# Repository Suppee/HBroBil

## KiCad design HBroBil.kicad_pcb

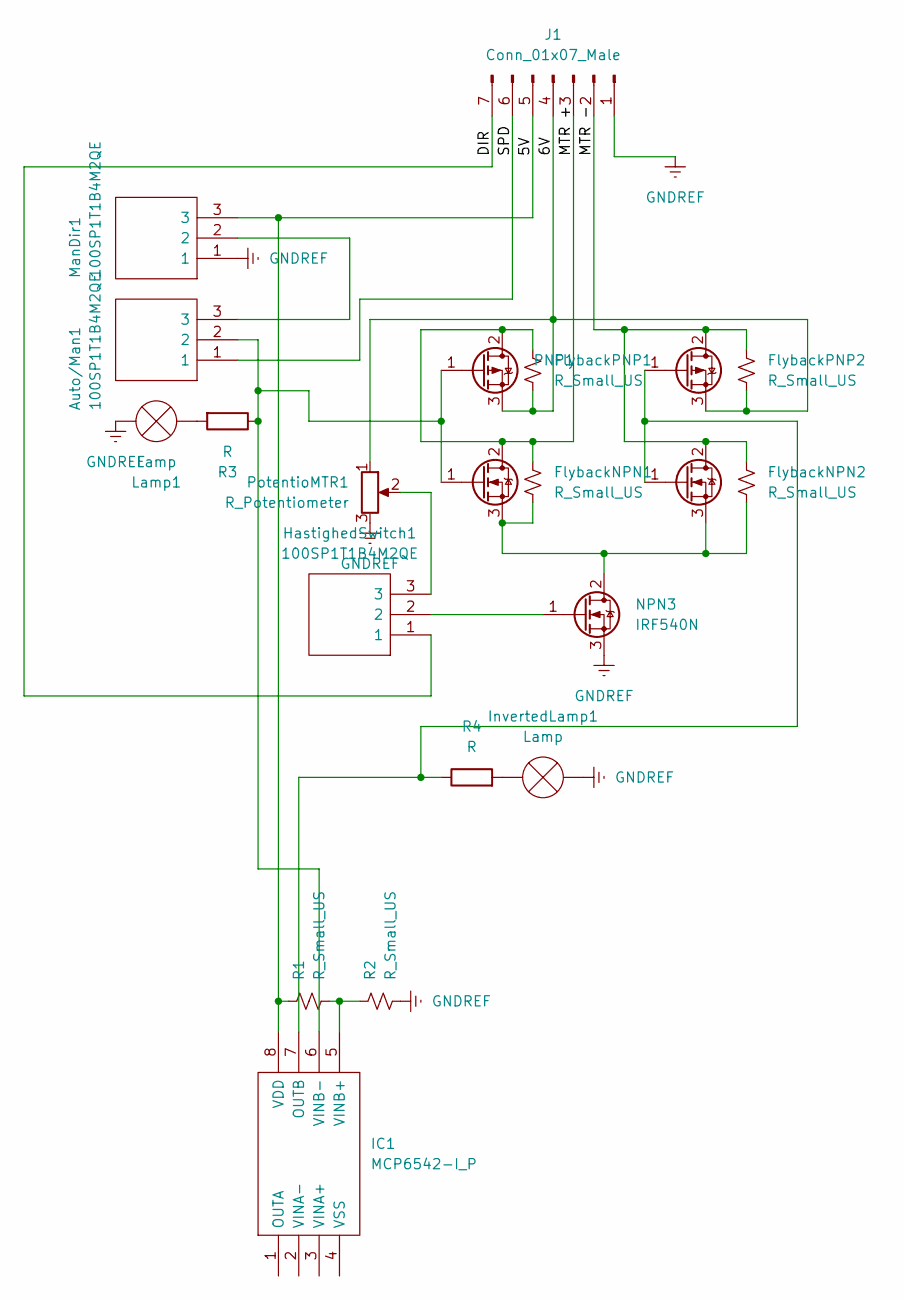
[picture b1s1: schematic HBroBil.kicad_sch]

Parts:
Auto/Man1: 100SP1T1B4M2QE; Manufacturer_Part_Number 100SP1T1B4M2QE; Mouser Part Number 612-100-A1421
FlybackNPN1, FlybackNPN2: R_Small_US; R_Axial_DIN0204_L3.6mm_D1.6mm_P7.62mm_Horizontal
FlybackPNP1, FlybackPNP2: R_Small_US; R_Axial_DIN0204_L3.6mm_D1.6mm_P7.62mm_Horizontal
HastighedSwitch1: 100SP1T1B4M2QE; Manufacturer_Part_Number 100SP1T1B4M2QE; Mouser Part Number 612-100-A1421
IC1: MCP6542-I_P; DIP781W56P254L950H533Q8N; Manufacturer_Part_Number MCP6542-I/P; Mouser Part Number 579-MCP6542-I/P
InvertedLamp1: Lamp; R_Axial_DIN0204_L3.6mm_D1.6mm_P2.54mm_Vertical
J1: Conn_01x07_Male; R_Array_SIP7
Lamp1: Lamp; R_Axial_DIN0204_L3.6mm_D1.6mm_P2.54mm_Vertical
ManDir1: 100SP1T1B4M2QE; Manufacturer_Part_Number 100SP1T1B4M2QE; Mouser Part Number 612-100-A1421
NPN1, NPN2, NPN3: IRF540N; TO-220-3_Vertical
PNP1, PNP2: IRF9540N; TO-220-3_Vertical
PotentioMTR1: R_Potentiometer; 100SP1T1B4M2QE
R1, R2: R_Small_US; R_Axial_DIN0204_L3.6mm_D1.6mm_P7.62mm_Horizontal
R3, R4: R; R_Axial_DIN0204_L3.6mm_D1.6mm_P7.62mm_Horizontal

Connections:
/5V: IC1.8 (VDD), J1.5, ManDir1.3, R1.1
/6V: FlybackPNP1.1, FlybackPNP2.1, J1.4, PNP1.3 (S), PNP2.3 (S), PotentioMTR1.1
/DIR: HastighedSwitch1.1, J1.7
/MTR +: FlybackNPN1.2, FlybackPNP1.2, J1.3, NPN1.2 (D), PNP1.2 (D)
/MTR -: FlybackNPN2.2, FlybackPNP2.2, J1.2, NPN2.2 (D), PNP2.2 (D)
/SPD: Auto/Man1.1, J1.6
GNDREF: IC1.4 (VSS), InvertedLamp1.1 (-), J1.1, Lamp1.1 (-), ManDir1.1, NPN3.3 (S), PotentioMTR1.3, R2.2
unnamed: Auto/Man1.2, IC1.6 (VINB-), NPN1.1 (G), PNP1.1 (G), R3.1
unnamed: Auto/Man1.3, ManDir1.2
unnamed: FlybackNPN1.1, FlybackNPN2.1, NPN1.3 (S), NPN2.3 (S), NPN3.2 (D)
unnamed: HastighedSwitch1.2, NPN3.1 (G)
unnamed: HastighedSwitch1.3, PotentioMTR1.2
unnamed: IC1.5 (VINB+), R1.2, R2.1
unnamed: IC1.7 (OUTB), NPN2.1 (G), PNP2.1 (G), R4.1
unnamed: InvertedLamp1.2 (+), R4.2
unnamed: Lamp1.2 (+), R3.2

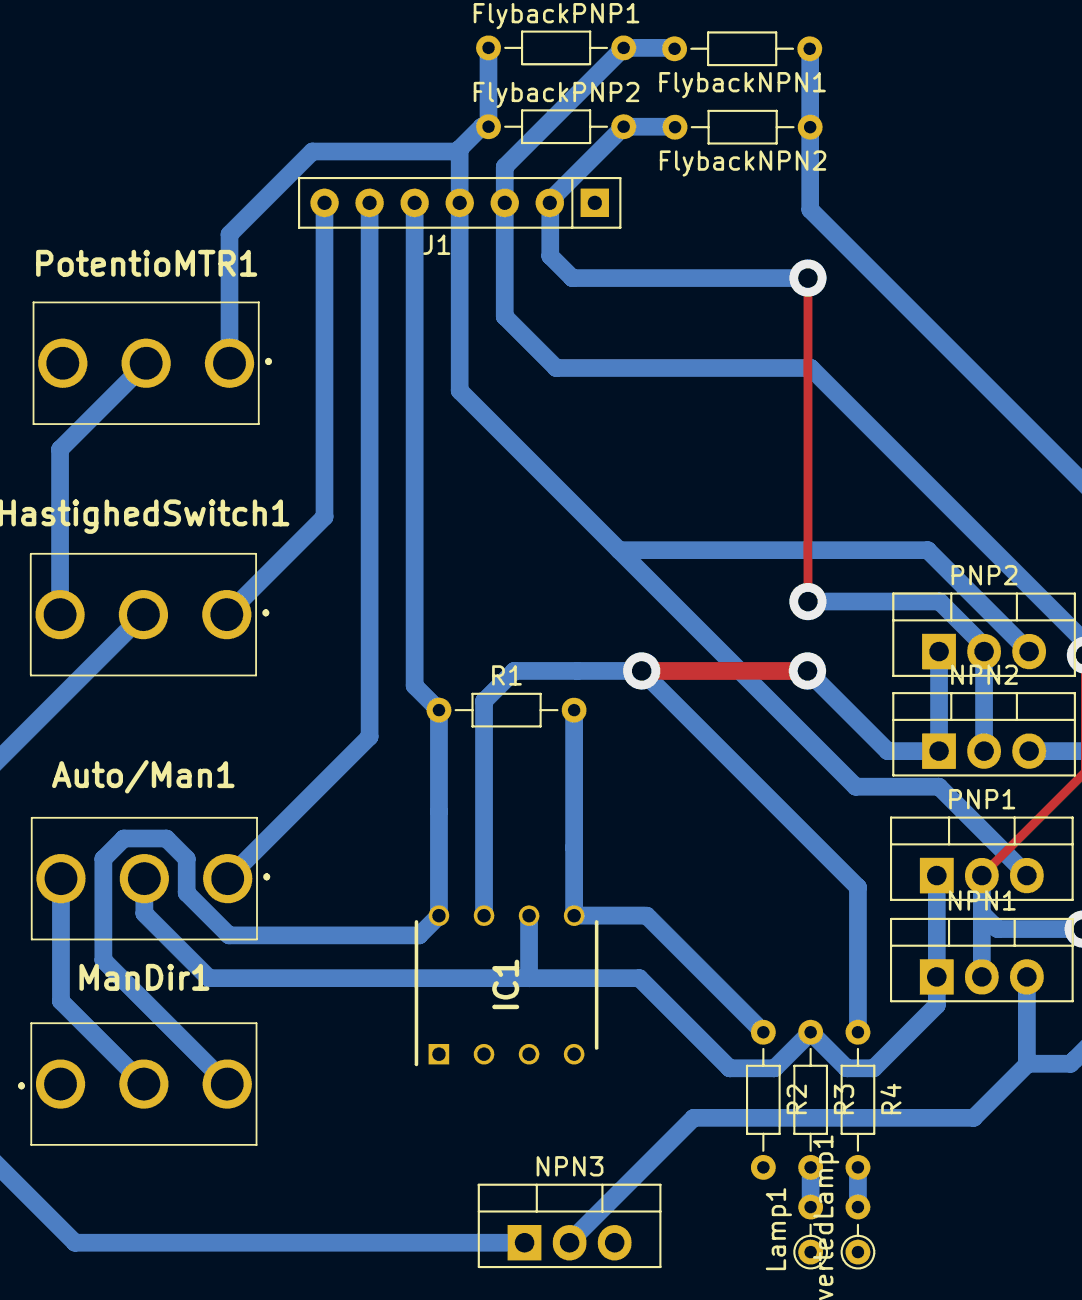
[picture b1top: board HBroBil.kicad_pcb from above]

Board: 2 copper layers, 21 parts (0 on the bottom side), 16 nets.

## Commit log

2022-05-11 HBridgeSetup
2022-05-19 Comparator component
2022-05-23 Finito
2022-05-23 Fixed wire corners
2022-05-23 Fixed wire Width, removed overlap connection
2022-05-23 Moar Fixz
2022-05-23 fixs
2022-05-24 Latest News
2022-05-24 hello
2022-05-24 Arduino-kode
2022-05-25 maybe is a workorino
2022-05-25 lAST FIXES
2022-05-26 Thicc
2022-05-31 Smol fix
2022-06-15 Fixes
